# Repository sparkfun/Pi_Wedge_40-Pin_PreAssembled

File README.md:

Pi Wedge 40-Pin PreAssembled - Breakout For 40-Pin, Second Generation Raspberry Pi GPIO Connector.
----------------------------

[SparkFun Pi Wedge (PreAssembled) [BOB-13717]](https://www.sparkfun.com/products/13717)

This part was created in Eagle v6.5.0.  Software examples were developed using the [WiringPi](http://wiringpi.com) libraries and utilities.

Repository Contents
-------------------

* **/Hardware** - All Eagle design files (.brd, .sch, .STL)
* **/Software** - C source code for SPI, I2C and GPIO examples.  All use [WiringPi](http://wiringpi.com) for the underlying device interfaces
* **/Production** - Production panel files (.brd)

Documentation
--------------
* **[Hookup Guide](https://learn.sparkfun.com/tutorials/preassembled-40-pin-pi-wedge-hookup-guide)** - Basic hookup guide for the Pi Wedge.
* **[Raspberry gPIo](https://learn.sparkfun.com/tutorials/raspberry-gpio)** - Programming guide using the Pi's I/O pins with Python and C. 
* **[Raspberry Pi SPI and I2C Tutorial](https://learn.sparkfun.com/tutorials/raspberry-pi-spi-and-i2c-tutorial)** - Programming guide using the Pi's SPI and I2C.
* **[SparkFun Fritzing repo](https://github.com/sparkfun/Fritzing_Parts)** - Fritzing diagrams for SparkFun products.
* **[SparkFun 3D Model repo](https://github.com/sparkfun/3D_Models)** - 3D models of SparkFun products. 
* **[SparkFun Graphical Datasheets](https://github.com/sparkfun/Graphical_Datasheets)** -Graphical Datasheets for various SparkFun products.

License Information
-------------------

This product is _**open source**_! 

Please review the LICENSE.md file for license information. 

If you have any questions or concerns on licensing, please contact techsupport@sparkfun.com.

Distributed as-is; no warranty is given.

- Your friends at SparkFun.

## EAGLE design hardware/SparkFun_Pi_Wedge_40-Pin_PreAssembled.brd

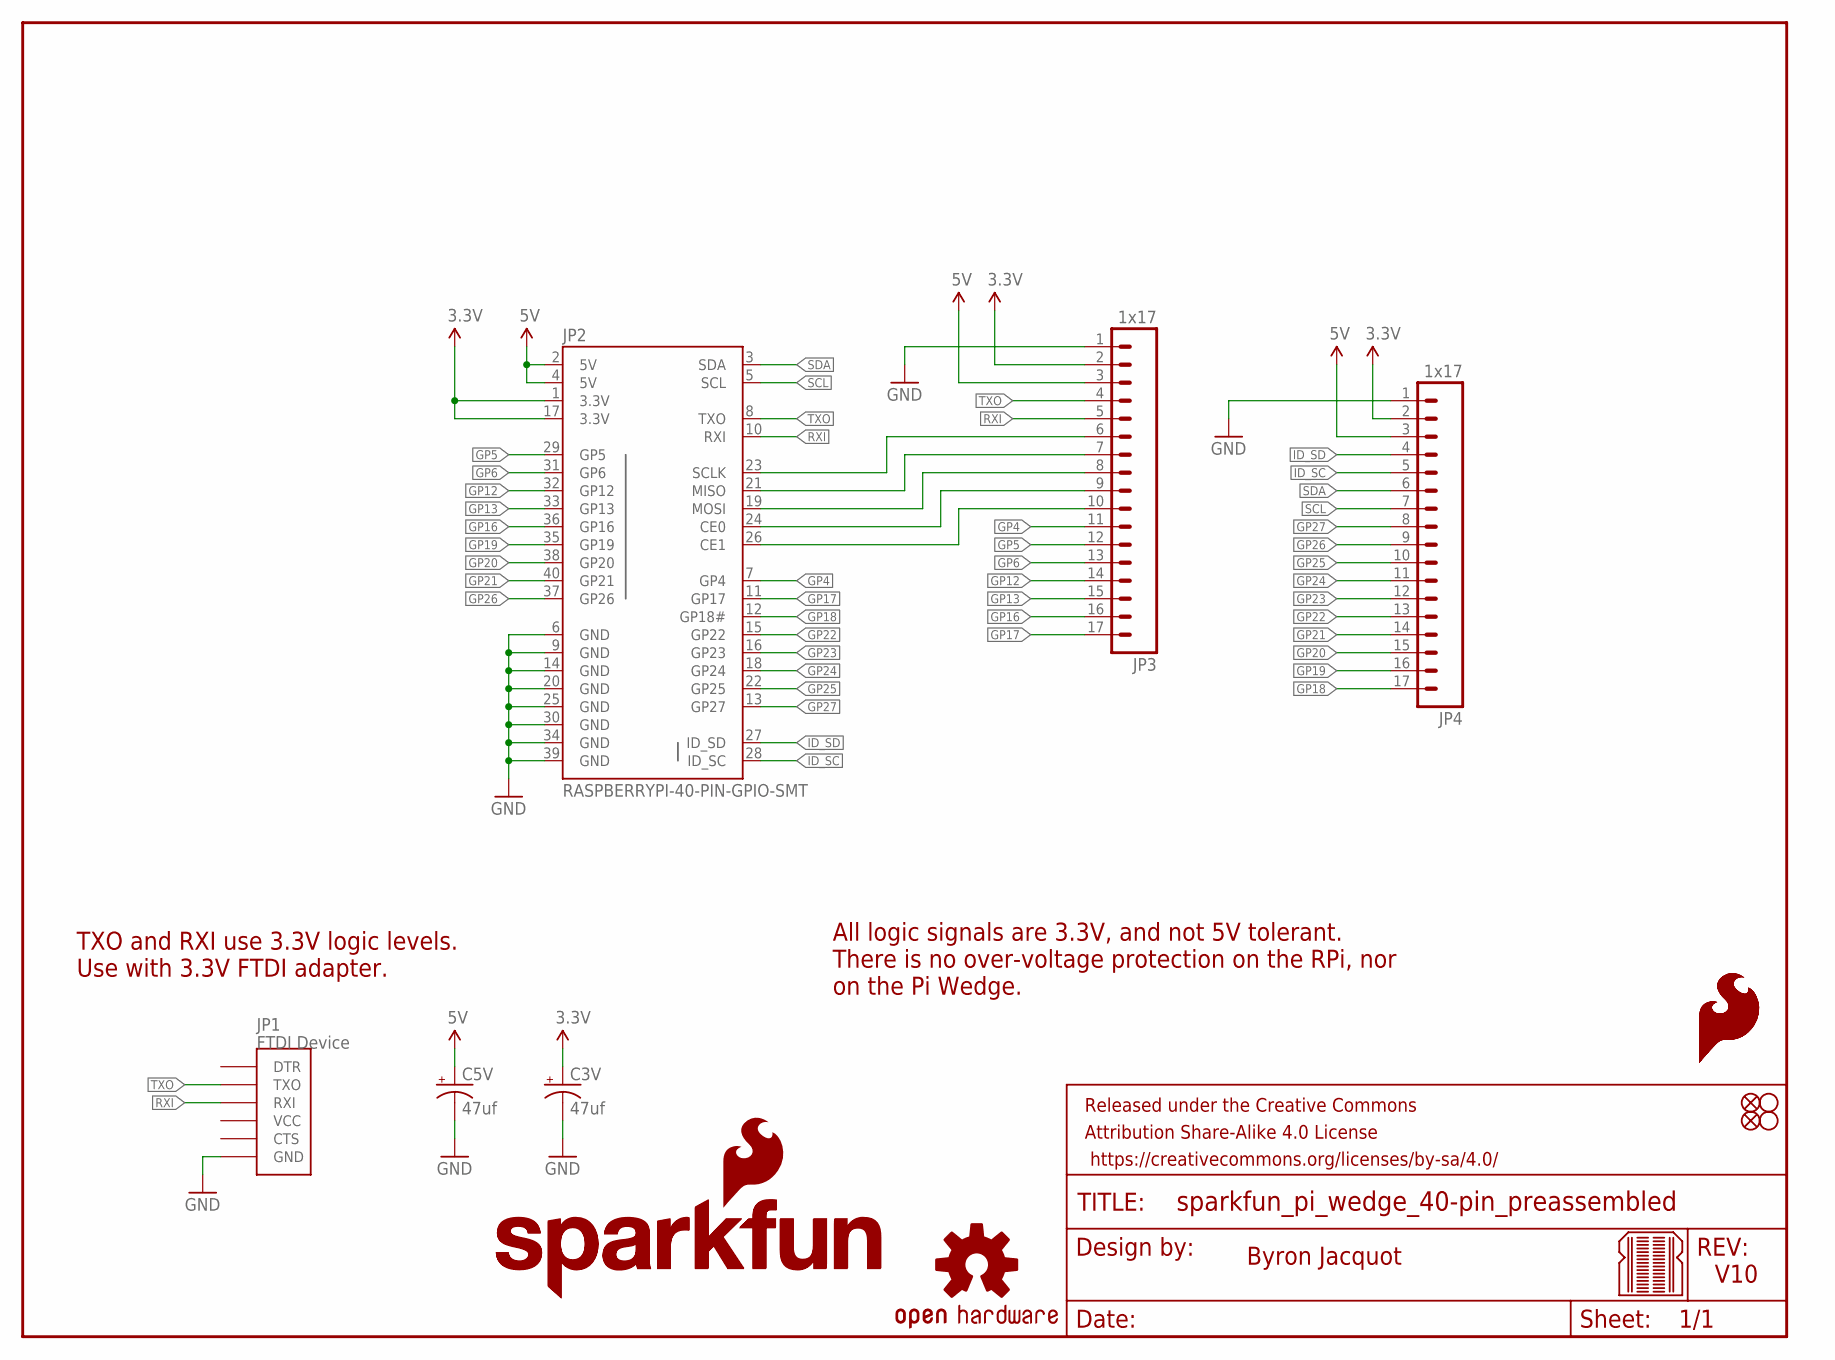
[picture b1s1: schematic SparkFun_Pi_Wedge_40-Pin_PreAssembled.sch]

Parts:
C3V, C5V: 47uf; PANASONIC_D
FID1, FID2: FIDUCIALUFIDUCIAL; MICRO-FIDUCIAL
FRAME2: FRAME-LETTER; CREATIVE_COMMONS
JP1: FTDI Device; FTDI_DEVICE_RA_SMT
JP2: RASPBERRYPI-40-PIN-GPIO-SMT; 2X20-SHROUDED-SMT
JP3, JP4: 1x17; 1X17_NO_SILK_KIT
LOGO1: SFE_LOGO_NAME.2_INCH; SFE_LOGO_NAME_.2
LOGO2: SFE_LOGO_NAME_FLAME.2_INCH; SFE_LOGO_NAME_FLAME_.2
LOGO3, LOGO4: SFE_LOGO_FLAME.1_INCH; SFE_LOGO_FLAME_.1
LOGO5: OSHW-LOGOS; OSHW-LOGO-S
STANDOFF1, STANDOFF2: STAND-OFF
U$2: BREADBOARD_PATTERN; BREADBOARD_SPACING

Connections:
3.3V: C3V.+, JP2.1 (3.3V), JP2.17 (3.3V), JP3.2, JP4.2
5V: C5V.+, JP2.2 (5V), JP2.4 (5V), JP3.3, JP4.3
CE0: JP2.24 (CE0), JP3.9
CE1: JP2.26 (CE1), JP3.10
GND: C3V.-, C5V.-, JP1.6 (GND), JP2.6 (GND), JP2.9 (GND), JP2.14 (GND), JP2.20 (GND), JP2.25 (GND), JP2.30 (GND), JP2.34 (GND), JP2.39 (GND), JP3.1, JP4.1
GP4: JP2.7 (GP4), JP3.11
GP5: JP2.29 (GP5), JP3.12
GP6: JP2.31 (GP6), JP3.13
GP12: JP2.32 (GP12), JP3.14
GP13: JP2.33 (GP13), JP3.15
GP16: JP2.36 (GP16), JP3.16
GP17: JP2.11 (GP17), JP3.17
GP18: JP2.12 (GP18#), JP4.17
GP19: JP2.35 (GP19), JP4.16
GP20: JP2.38 (GP20), JP4.15
GP21: JP2.40 (GP21), JP4.14
GP22: JP2.15 (GP22), JP4.13
GP23: JP2.16 (GP23), JP4.12
GP24: JP2.18 (GP24), JP4.11
GP25: JP2.22 (GP25), JP4.10
GP26: JP2.37 (GP26), JP4.9
GP27: JP2.13 (GP27), JP4.8
ID_SC: JP2.28 (ID_SC), JP4.5
ID_SD: JP2.27 (ID_SD), JP4.4
MISO: JP2.21 (MISO), JP3.7
MOSI: JP2.19 (MOSI), JP3.8
RXI: JP1.3 (RXI), JP2.10 (RXI), JP3.5
SCL: JP2.5 (SCL), JP4.7
SCLK: JP2.23 (SCLK), JP3.6
SDA: JP2.3 (SDA), JP4.6
TXO: JP1.2 (TXO), JP2.8 (TXO), JP3.4

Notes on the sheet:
Byron Jacquot
V10
All logic signals are 3.3V, and not 5V tolerant. There is no over-voltage protection on the RPi, nor on the Pi Wedge.
TXO and RXI use 3.3V logic levels. Use with 3.3V FTDI adapter.

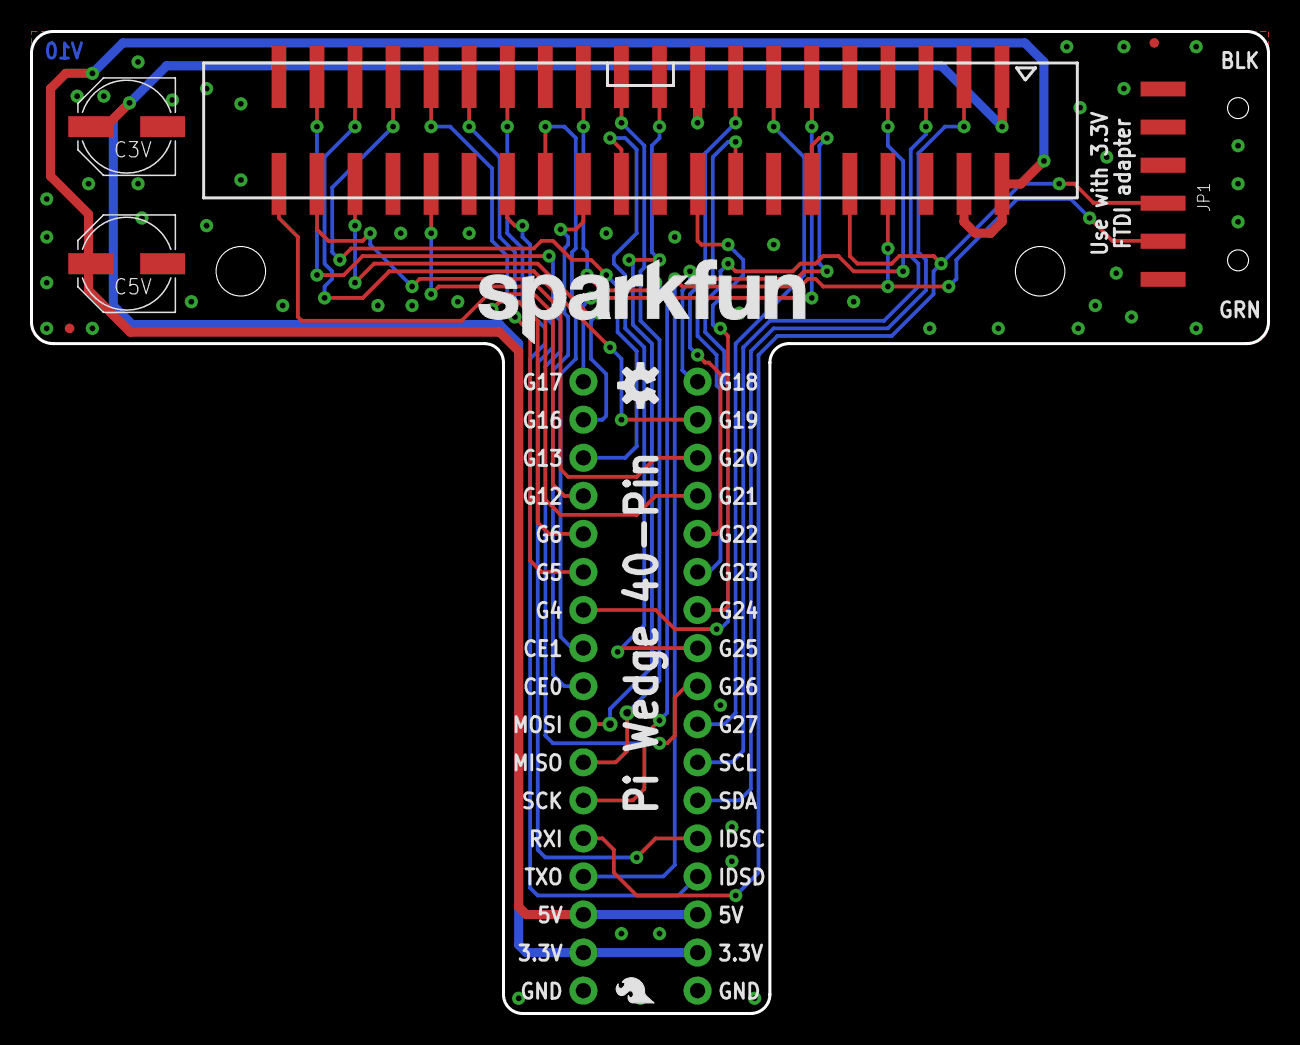
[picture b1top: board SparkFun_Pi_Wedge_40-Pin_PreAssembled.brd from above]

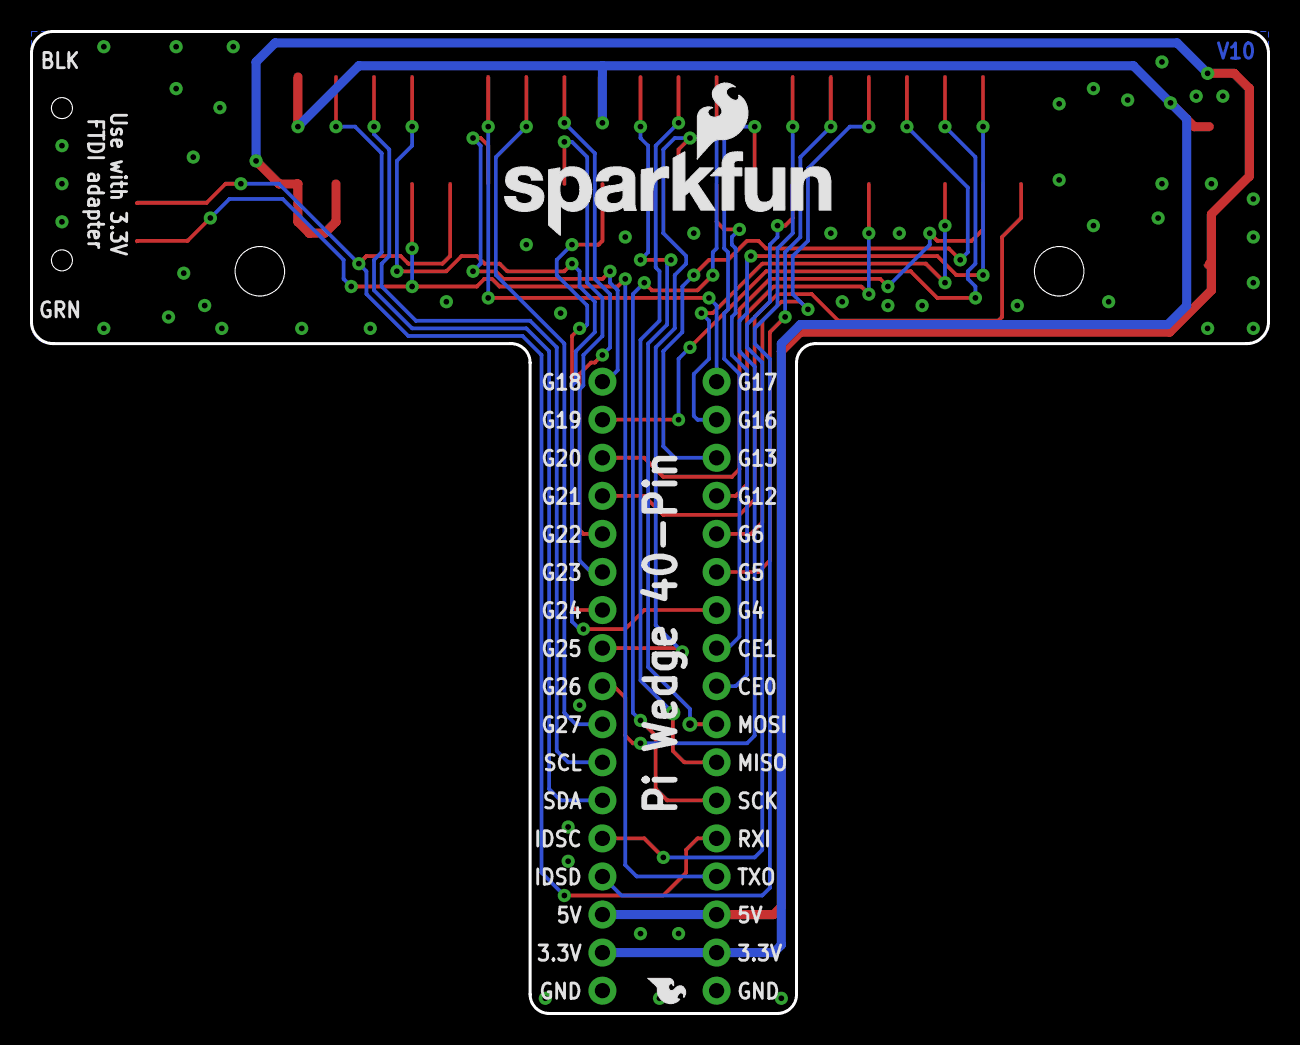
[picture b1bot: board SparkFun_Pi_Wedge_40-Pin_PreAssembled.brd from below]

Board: 2 copper layers, 82.5 x 65.5 mm, 17 parts (4 on the bottom side), 31 nets.

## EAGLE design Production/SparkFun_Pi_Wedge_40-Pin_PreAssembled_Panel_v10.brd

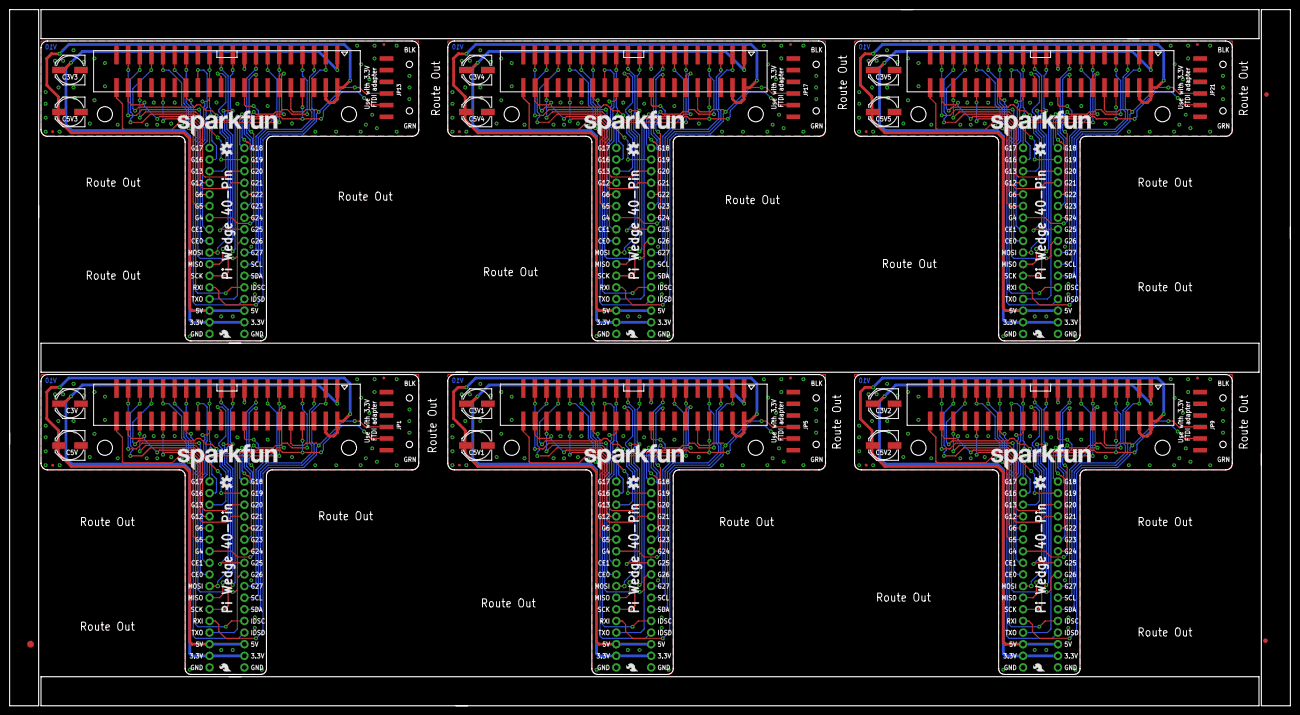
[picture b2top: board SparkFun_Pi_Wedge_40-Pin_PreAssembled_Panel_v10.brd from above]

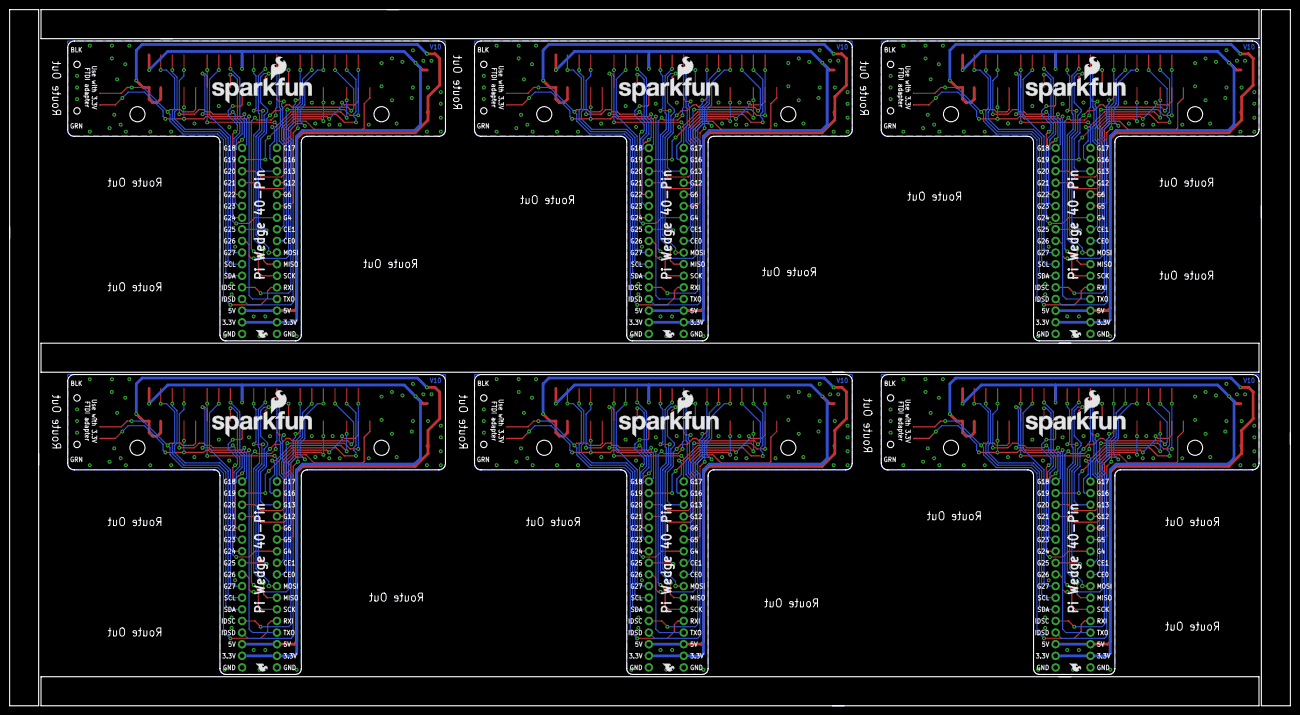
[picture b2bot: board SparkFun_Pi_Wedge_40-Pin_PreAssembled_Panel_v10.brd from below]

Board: 2 copper layers, 279.9 x 152.1 mm, 93 parts (24 on the bottom side), 186 nets.

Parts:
C3V, C3V1, C3V2, C3V3, C3V4, C3V5, C5V, C5V1, C5V2, C5V3, C5V4, C5V5: 10uf; PANASONIC_D
E$1: FIDUCIAL-1.5X3
E$5, E$6: FIDUCIAL-1X2
FID1, FID2, FID3, FID4, FID5, FID6, FID7, FID8, FID9, FID10, FID11, FID12: FIDUCIALUFIDUCIAL; MICRO-FIDUCIAL
JP1, JP5, JP9, JP13, JP17, JP21: FTDI Device; FTDI_DEVICE_RA_SMT
JP2, JP6, JP10, JP14, JP18, JP22: RASPBERRYPI-40-PIN-GPIO-SMT; 2X20-SHROUDED-SMT
JP3, JP4, JP7, JP8, JP11, JP12, JP15, JP16, JP19, JP20, JP23, JP24: 1x17; 1X17_NO_SILK_KIT
LOGO1, LOGO6, LOGO11, LOGO16, LOGO21, LOGO26: SFE_LOGO_NAME.2_INCH; SFE_LOGO_NAME_.2
LOGO2, LOGO7, LOGO12, LOGO17, LOGO22, LOGO27: SFE_LOGO_NAME_FLAME.2_INCH; SFE_LOGO_NAME_FLAME_.2
LOGO3, LOGO4, LOGO8, LOGO9, LOGO13, LOGO14, LOGO18, LOGO19, LOGO23, LOGO24, LOGO28, LOGO29: SFE_LOGO_FLAME.1_INCH; SFE_LOGO_FLAME_.1
LOGO5, LOGO10, LOGO15, LOGO20, LOGO25, LOGO30: OSHW-LOGOS; OSHW-LOGO-S
STANDOFF1, STANDOFF2, STANDOFF3, STANDOFF4, STANDOFF5, STANDOFF6, STANDOFF7, STANDOFF8, STANDOFF9, STANDOFF10, STANDOFF11, STANDOFF12: STAND-OFF

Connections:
3.3V: C3V.+, JP2.1, JP2.17, JP3.2, JP4.2
3.3V1: C3V1.+, JP6.1, JP6.17, JP7.2, JP8.2
3.3V2: C3V2.+, JP10.1, JP10.17, JP11.2, JP12.2
3.3V3: C3V3.+, JP14.1, JP14.17, JP15.2, JP16.2
3.3V4: C3V4.+, JP18.1, JP18.17, JP19.2, JP20.2
3.3V5: C3V5.+, JP22.1, JP22.17, JP23.2, JP24.2
5V: C5V.+, JP2.2, JP2.4, JP3.3, JP4.3
5V1: C5V1.+, JP6.2, JP6.4, JP7.3, JP8.3
5V2: C5V2.+, JP10.2, JP10.4, JP11.3, JP12.3
5V3: C5V3.+, JP14.2, JP14.4, JP15.3, JP16.3
5V4: C5V4.+, JP18.2, JP18.4, JP19.3, JP20.3
5V5: C5V5.+, JP22.2, JP22.4, JP23.3, JP24.3
CE0: JP2.24, JP3.9
CE1: JP2.26, JP3.10
CE2: JP6.24, JP7.9
CE3: JP6.26, JP7.10
CE4: JP10.24, JP11.9
CE5: JP10.26, JP11.10
CE6: JP14.24, JP15.9
CE7: JP14.26, JP15.10
CE8: JP18.24, JP19.9
CE9: JP18.26, JP19.10
CE10: JP22.24, JP23.9
CE11: JP22.26, JP23.10
GND: C3V.-, C5V.-, JP1.6, JP2.6, JP2.9, JP2.14, JP2.20, JP2.25, JP2.30, JP2.34, JP2.39, JP3.1, JP4.1
GND1: C3V1.-, C5V1.-, JP5.6, JP6.6, JP6.9, JP6.14, JP6.20, JP6.25, JP6.30, JP6.34, JP6.39, JP7.1, JP8.1
GND2: C3V2.-, C5V2.-, JP9.6, JP10.6, JP10.9, JP10.14, JP10.20, JP10.25, JP10.30, JP10.34, JP10.39, JP11.1, JP12.1
GND3: C3V3.-, C5V3.-, JP13.6, JP14.6, JP14.9, JP14.14, JP14.20, JP14.25, JP14.30, JP14.34, JP14.39, JP15.1, JP16.1
GND4: C3V4.-, C5V4.-, JP17.6, JP18.6, JP18.9, JP18.14, JP18.20, JP18.25, JP18.30, JP18.34, JP18.39, JP19.1, JP20.1
GND5: C3V5.-, C5V5.-, JP21.6, JP22.6, JP22.9, JP22.14, JP22.20, JP22.25, JP22.30, JP22.34, JP22.39, JP23.1, JP24.1
GP1: JP6.7, JP7.11
GP2: JP6.13, JP8.8
GP3: JP6.22, JP8.10
GP4: JP2.7, JP3.11
GP5: JP2.29, JP3.12
GP6: JP2.31, JP3.13
GP7: JP6.18, JP8.11
GP8: JP6.16, JP8.12
GP9: JP6.15, JP8.13
GP10: JP6.12, JP8.17
GP11: JP6.11, JP7.17
GP12: JP2.32, JP3.14
GP13: JP2.33, JP3.15
GP14: JP6.29, JP7.12
GP15: JP6.31, JP7.13
GP16: JP2.36, JP3.16
GP17: JP2.11, JP3.17
GP18: JP2.12, JP4.17
GP19: JP2.35, JP4.16
GP20: JP2.38, JP4.15
GP21: JP2.40, JP4.14
GP22: JP2.15, JP4.13
GP23: JP2.16, JP4.12
GP24: JP2.18, JP4.11
GP25: JP2.22, JP4.10
GP26: JP2.37, JP4.9
GP27: JP2.13, JP4.8
GP28: JP6.32, JP7.14
GP29: JP6.33, JP7.15
GP30: JP6.36, JP7.16
GP31: JP6.35, JP8.16
GP32: JP6.38, JP8.15
GP33: JP6.40, JP8.14
GP34: JP6.37, JP8.9
GP35: JP10.7, JP11.11
GP36: JP10.13, JP12.8
GP37: JP10.22, JP12.10
GP38: JP10.18, JP12.11
GP39: JP10.16, JP12.12
GP40: JP10.15, JP12.13
GP41: JP10.12, JP12.17
GP42: JP10.11, JP11.17
GP43: JP10.29, JP11.12
GP44: JP10.31, JP11.13
GP45: JP10.32, JP11.14
GP46: JP10.33, JP11.15
GP47: JP10.36, JP11.16
GP48: JP10.35, JP12.16
GP49: JP10.38, JP12.15
GP50: JP10.40, JP12.14
GP51: JP10.37, JP12.9
GP52: JP14.7, JP15.11
GP53: JP14.13, JP16.8
GP54: JP14.22, JP16.10
GP55: JP14.18, JP16.11
GP56: JP14.16, JP16.12
GP57: JP14.15, JP16.13
GP58: JP14.12, JP16.17
GP59: JP14.11, JP15.17
GP60: JP14.29, JP15.12
GP61: JP14.31, JP15.13
GP62: JP14.32, JP15.14
GP63: JP14.33, JP15.15
GP64: JP14.36, JP15.16
GP65: JP14.35, JP16.16
GP66: JP14.38, JP16.15
GP67: JP14.40, JP16.14
GP68: JP14.37, JP16.9
GP69: JP18.7, JP19.11
GP70: JP18.13, JP20.8
GP71: JP18.22, JP20.10
GP72: JP18.18, JP20.11
GP73: JP18.16, JP20.12
GP74: JP18.15, JP20.13
GP75: JP18.12, JP20.17
GP76: JP18.11, JP19.17
GP77: JP18.29, JP19.12
GP78: JP18.31, JP19.13
GP79: JP18.32, JP19.14
GP80: JP18.33, JP19.15
GP81: JP18.36, JP19.16
GP82: JP18.35, JP20.16
GP83: JP18.38, JP20.15
GP84: JP18.40, JP20.14
GP85: JP18.37, JP20.9
GP86: JP22.7, JP23.11
GP87: JP22.13, JP24.8
GP88: JP22.22, JP24.10
GP89: JP22.18, JP24.11
GP90: JP22.16, JP24.12
GP91: JP22.15, JP24.13
GP92: JP22.12, JP24.17
GP93: JP22.11, JP23.17
GP94: JP22.29, JP23.12
GP95: JP22.31, JP23.13
GP96: JP22.32, JP23.14
GP97: JP22.33, JP23.15
GP98: JP22.36, JP23.16
GP99: JP22.35, JP24.16
GP100: JP22.38, JP24.15
GP101: JP22.40, JP24.14
GP102: JP22.37, JP24.9
ID_SC: JP2.28, JP4.5
ID_SC1: JP6.28, JP8.5
ID_SC2: JP10.28, JP12.5
ID_SC3: JP14.28, JP16.5
ID_SC4: JP18.28, JP20.5
ID_SC5: JP22.28, JP24.5
ID_SD: JP2.27, JP4.4
ID_SD1: JP6.27, JP8.4
ID_SD2: JP10.27, JP12.4
ID_SD3: JP14.27, JP16.4
ID_SD4: JP18.27, JP20.4
ID_SD5: JP22.27, JP24.4
MISO: JP2.21, JP3.7
MISO1: JP6.21, JP7.7
MISO2: JP10.21, JP11.7
MISO3: JP14.21, JP15.7
MISO4: JP18.21, JP19.7
MISO5: JP22.21, JP23.7
MOSI: JP2.19, JP3.8
MOSI1: JP6.19, JP7.8
MOSI2: JP10.19, JP11.8
MOSI3: JP14.19, JP15.8
MOSI4: JP18.19, JP19.8
MOSI5: JP22.19, JP23.8
RXI: JP1.3, JP2.10, JP3.5
RXI1: JP5.3, JP6.10, JP7.5
RXI2: JP9.3, JP10.10, JP11.5
RXI3: JP13.3, JP14.10, JP15.5
RXI4: JP17.3, JP18.10, JP19.5
RXI5: JP21.3, JP22.10, JP23.5
SCL: JP2.5, JP4.7
SCL1: JP6.5, JP8.7
SCL2: JP10.5, JP12.7
SCL3: JP14.5, JP16.7
SCL4: JP18.5, JP20.7
SCL5: JP22.5, JP24.7
SCLK: JP2.23, JP3.6
SCLK1: JP6.23, JP7.6
SCLK2: JP10.23, JP11.6
SCLK3: JP14.23, JP15.6
SCLK4: JP18.23, JP19.6
SCLK5: JP22.23, JP23.6
SDA: JP2.3, JP4.6
SDA1: JP6.3, JP8.6
SDA2: JP10.3, JP12.6
SDA3: JP14.3, JP16.6
SDA4: JP18.3, JP20.6
SDA5: JP22.3, JP24.6
TXO: JP1.2, JP2.8, JP3.4
TXO1: JP5.2, JP6.8, JP7.4
TXO2: JP9.2, JP10.8, JP11.4
TXO3: JP13.2, JP14.8, JP15.4
TXO4: JP17.2, JP18.8, JP19.4
TXO5: JP21.2, JP22.8, JP23.4

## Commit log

2015-07-30 Initial comit
    Files copied from the PTH Kit version.
2015-07-30 Parts swapped, & old traces ripped up.
    Ready for routing through the narrow neck.
2015-07-31 The hard part is routed.
    Ready for Review.
2015-08-10 A few touch-ups before review.
2015-08-10 Updating LICENSE.md
2015-08-11 Added missing PROD_IDs.
    Also apparently picked up huge changes from logo revamp in aesthetics
    library. This commit is huge, but with no physical changes to board or
    schematic.
2015-08-13 Fixing review issues.
2015-09-21 Updates after group review.
    A few silk touch-ups.
    Renaming to "Pi Wedge 40-Pin".
2015-09-22 Updates after checklist review.
2015-09-22 Readme updates.
    Trying to get naming decoupled from Pi revisions.
2015-09-22 created panel v10
2015-10-08 Updating caps values.
    It had 47uf library parts (CAP-10547), but the schem incorrectly showed
    10uf as the value.
    Schem now reads 47uf.
2015-10-27 Adding software examples.
    Just FTP'd off a working Pi.
2016-06-15 increased paste layer on 40-pin connector
2016-09-20 Updating product links in README
2022-08-10 fix WiringPi link

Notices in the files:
parts and their libraries:
SparkFun-Connectors: Licensing: CC v3.0 Share-Alike You are welcome to use this library for commercial purposes.
SparkFun-Retired: Licensing:Creative Commons ShareAlike 4.0 International - https://creativecommons.org/licenses/by-sa/4.0
SparkFun-Aesthetics: Released under the Creative Commons
